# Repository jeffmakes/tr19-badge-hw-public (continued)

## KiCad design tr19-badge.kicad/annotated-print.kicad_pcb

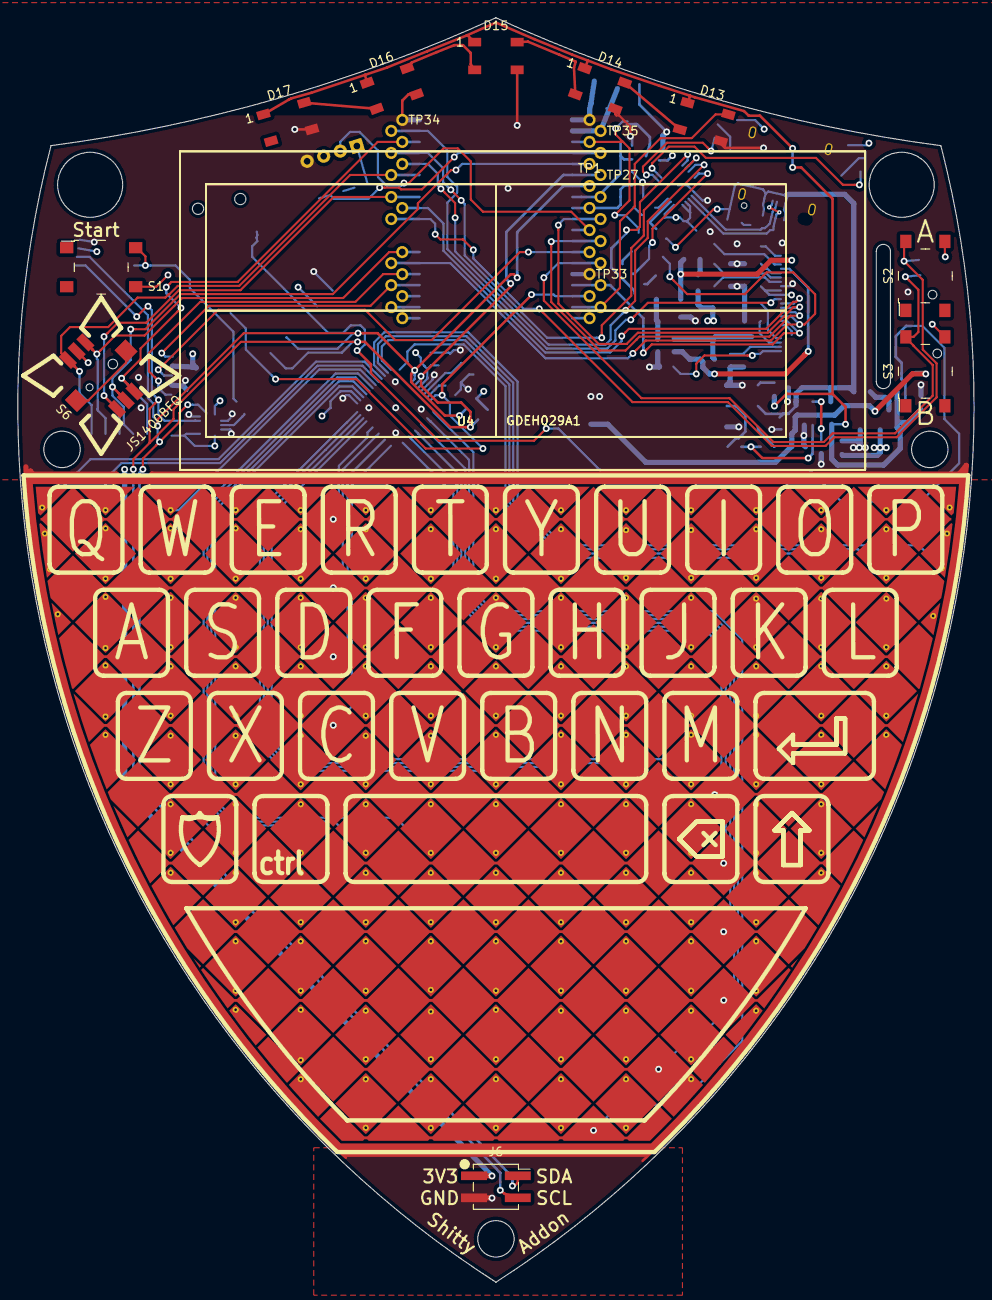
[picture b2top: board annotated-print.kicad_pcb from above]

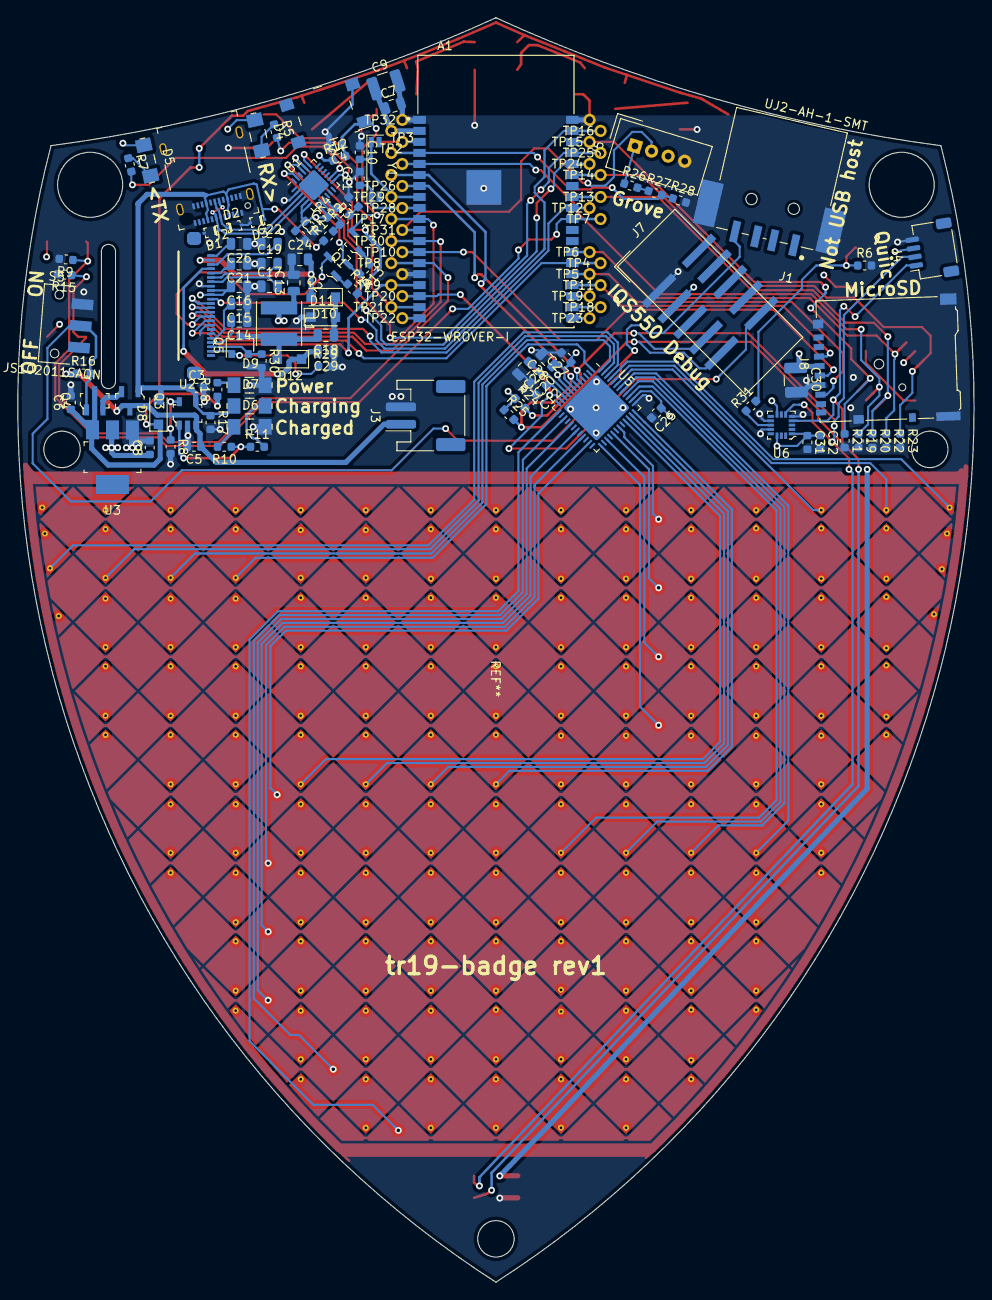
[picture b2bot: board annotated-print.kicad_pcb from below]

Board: 4 copper layers, 110.2 x 145.8 mm, 145 parts (127 on the bottom side), 108 nets.

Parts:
A1: ESP32-WROVER-I; XCVR_ESP32-WROVER-I
A2: tr19_touch_array; electrode-array-2
C1, C3, C5, C6, C8, C31: 4.7uF; C_0603_1608Metric
C2, C4, C12, C25, C32: 100nF; C_0603_1608Metric
C7, C23, C28: 1uF; C_0805_2012Metric
C9, C30: 100uF; C_1210_3225Metric
C10, C11: 10pF; C_0603_1608Metric
C13, C18: 4.7uF 50V; C_0805_2012Metric
C14, C15, C16, C17, C19, C21, C22, C24, C26, C29: 1uF 50V; C_0805_2012Metric
C20, C27: 100pF; C_0603_1608Metric
D1, D2, D3: ESD5Z6.0T5G; SOD-523-numbered-pads
D4, D6: LTST-C150KGKT; 1206
D5, D7: LTST-C150KFKT; 1206
D8, D10, D11, D12: DSS13UTR; D_SOD-123F
D9: LTST-C150KSKT; 1206
D13, D14, D15, D16, D17: WS2812B; LED_WS2812B_PLCC4_5.0x5.0mm_P3.2mm_no-silk
J1: UJ2-AH-1-SMT; CUI_UJ2-AH-1-SMT
J2: 12401610E4_2A; USB_Type_C_Female__12401610E4_2A
J3: S2B-PH-SM4-TB; JST_PH_S2B-PH-SM4-TB_1x02-1MP_P2.00mm_Horizontal
J4: Conn_01x04; JST_SH_SM04B-SRSS-TB_1x04-1MP_P1.00mm_Horizontal
J5: Conn_01x04; NS-Tech_Grove_1x04_P2mm_Vertical
J6: M20-7870246; PinSocket_2x02_P2.54mm_Vertical_SMD
J7: 3020-10-0300-00; IDC-Header_2x05_P2.54mm_Vertical_SMD
J8: Micro_SD_Card_Det_Hirose_DM3AT; microSD_HC_Hirose_DM3AT-SF-PEJM5
L1: 10uH 1A; L_Taiyo-Yuden_MD-5050
Q1, Q2: MMBT3904-TP; SOT-23-3
Q3, Q4: DMG2305UX-13; SOT-23-3
Q5: SSM3K376R; SOT-23
R1, R2, R3, R6, R9, R12, R13, R14, R15, R16, R17, R19, R20, R21, R22, R23, R24, R25, R29: 10k; R_0603_1608Metric
R4, R5, R7, R8, R10, R11, R18, R31: 1k; R_0603_1608Metric
R26, R27, R28: 100k; R_0603_1608Metric
R30: 3R; R_0603_1608Metric
S1, S2, S3, S4: PTS645SM43SMTR92_LFS; Switch_Tactile_SMD_6x6mm_PTS645
S5: JS102011SAQN; SW_JS102011SAQN
S6: JS1400BFQ; SW_JS1400BFQ-arrows
TP1, TP2, TP3, TP4, TP5, TP6, TP7, TP8, TP9, TP10, TP11, TP12, TP13, TP14, TP15, TP16, TP17, TP18, TP19, TP20, TP21, TP22, TP23, TP24, TP25, TP26, TP27, TP28, TP29, TP30, TP31, TP32, TP33, TP34, TP35: test-pad-1.4-TH
U1: CP2102N-A01-GQFN24; QFN-24-1EP_4x4mm_P0.5mm_EP2.6x2.6mm
U2: MCP73831T-2ACI_OT; SOT-753
U3: AP2114H-3_3TRG1; SOT-223
U4, U4#2: GDEH029A1
U5: IQS550; QFN-48-1EP_7x7mm_P0.5mm_EP5.45x5.45mm
U6: LIS3DHTR; VFLGA-16_3x3mm
Y1: 32.768kHz; Crystal_SMD_SeikoEpson_MC146-4Pin_6.7x1.5mm

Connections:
+3V3: A1.2, C1.1, C2.1, C7.1, C8.1, C9.1, C13.1, C16.2, C25.1, C27.1, C28.1, C30.1, C31.1, C32.1, D4.1, D5.1, J4.3, J5.3, J6.2, J7.3, J8.4, L1.1, R4.1, R12.1, R24.1, R25.1, S1.4, S2.4, S3.4, S6.5, TP35.1, U1.5, U1.6, U1.7, U3.2, U4.15, U4.16, U4#2.15, U4#2.16, U5.7, U5.38, U6.1, U6.8, U6.14
+BATT: C5.1, J3.1, Q3.3, R16.1, U2.3
+VSW: C6.1, D8.1, D13.1, D14.1, D15.1, D16.1, D17.1, Q4.3, R18.1, U3.3
/32K_XN: A1.9, C11.1, TP28.1, Y1.2
/32K_XP: A1.8, C10.2, TP29.1, Y1.1
/ACCEL_INT: R31.1, U6.11
/BTN_A: A1.29, R9.1, S2.2, TP7.1
/BTN_B: A1.14, R15.1, S3.2, TP8.1
/BTN_START: R6.1, R31.2, S1.2
/BUSY: A1.16, TP9.1, U4.9, U4#2.9
/DTR: Q2.2, R13.2, U1.23
/EN: A1.3, C4.1, Q1.3, R12.2, S4.1, TP3.1
/GDR: Q5.1, R29.1, U4.2, U4#2.2
/GV_SIG0: J5.1, R26.1
/GV_SIG0_DIV: A1.4, R27.2, R28.1, TP2.1
/GV_SIG1: A1.11, J5.2, TP31.1
/IO0: A1.25, Q2.3, TP4.1, U4.10, U4#2.10
/IQ_RDY: A1.17, J7.10, TP20.1, U5.11
/JOY_A: A1.31, R20.1, S6.1, TP13.1
/JOY_B: A1.33, R23.1, S6.4, TP14.1
/JOY_C: A1.36, R21.1, S6.3, TP15.1
/JOY_D: A1.26, R22.1, S6.6, TP6.1
/JOY_PUSH: A1.5, R19.1, S6.2, TP1.1
/LED_DIN: A1.18, D13.4, TP21.1
/MOSI: A1.37, TP16.1, U4.14, U4#2.14
/PREVGH: C29.2, D12.1, U4.21, U4#2.21
/PREVGL: C24.2, D10.2, U4.23, U4#2.23
/RESE: Q5.2, R30.1, U4.3, U4#2.3
/RTS: Q1.2, R14.2, U1.19
/RXD0: A1.34, TP24.1, U1.21
/RXT: R5.2, U1.13
/Rx0A: A2.RX9, U5.13
/Rx1A: A2.RX8, U5.15
/Rx2A: A2.RX7, U5.17
/Rx3A: A2.RX6, U5.19
/Rx4A: A2.RX5, U5.21
/Rx5A: A2.RX4, U5.23
/Rx6A: A2.RX3, U5.25
/Rx7A: A2.RX2, U5.27
/Rx8A: A2.RX1, U5.29
/Rx9A: A2.RX0, U5.31
/SCK: A1.30, TP12.1, U4.13, U4#2.13
/SCL: A1.6, J4.1, J6.3, J7.9, R25.2, TP27.1, U5.6, U6.4
/SDA: A1.7, J4.2, J6.1, J7.7, R24.2, TP26.1, U5.5, U6.6
/SD_CLK: A1.13, J8.5, TP10.1
/SD_CMD: A1.23, J8.3, TP11.1
/SD_DAT0: A1.24, J8.7, TP5.1
/TXD0: A1.35, TP25.1, U1.20
/TXT: R7.2, U1.14
/Tx0: A2.TX10, U5.33
/Tx1: A2.TX9, U5.34
/Tx2: A2.TX8, U5.35
/Tx3: A2.TX7, U5.36
/Tx4: A2.TX6, U5.39
/Tx5: A2.TX5, U5.40
/Tx6: A2.TX4, U5.41
/Tx7: A2.TX3, U5.42
/Tx8: A2.TX2, U5.43
/Tx9: A2.TX1, U5.44
/Tx10: A2.TX0, U5.45
/Tx11: A2.TX14, U5.46
/Tx12: A2.TX13, U5.47
/Tx13: A2.TX12, U5.48
/Tx14: A2.TX11, U5.1
/USB_DN: D1.1, J2.A7, J2.B7, U1.4
/USB_DP: D2.1, J2.A6, J2.B6, U1.3
/_reserved_gpio6: A1.20, TP23.1
/_reserved_gpio7: A1.21, TP18.1
/_reserved_gpio8: A1.22, TP19.1
/_reserved_gpio11: A1.19, TP22.1
/d_VCOM: C26.2, U4.24, U4#2.24
/d_VDD: C17.2, U4.18, U4#2.18
/d_VGH: C15.2, U4.5, U4#2.5
/d_VGL: C14.2, U4.4, U4#2.4
/d_VPP: C19.2, U4.19, U4#2.19
/d_VSH: C21.2, U4.20, U4#2.20
/d_VSL: C22.2, U4.22, U4#2.22
/~CS~: A1.10, TP17.1, U4.12, U4#2.12
/~DC~: A1.12, TP30.1, U4.11, U4#2.11
/~PWR_EN~: J1.4, Q4.1, R16.2, S5.2
GND: A1.1, A1.15, A1.38, A1.39, A2.GND, C1.2, C2.2, C3.2, C4.2, C5.2, C6.2, C7.2, C8.2, C9.2, C10.1, C11.2, C12.2, C13.2, C14.1, C15.1, C16.1, C17.1, C19.1, C20.2, C21.1, C22.1, C23.2, C24.1, C25.2, C26.1, C27.2, C28.2, C29.1, C30.2, C31.2, C32.2, D1.2, D2.2, D3.2, D6.2, D9.2, D11.1, D13.3, D14.3, D15.3, D16.3, D17.3, J1.S1, J1.S2, J2.A1, J2.A12, J2.B1, J2.B12, J2.SH, J3.2, J4.4, J5.4, J6.4, J7.1, J8.6, J8.11, R3.2, R6.2, R8.2, R9.2, R15.2, R17.2, R19.2, R20.2, R21.2, R22.2, R23.2, R28.2, R29.2, R30.2, S4.3, S5.1, TP32.1, TP33.1, TP34.1, U1.2, U1.25, U2.2, U3.1, U4.8, U4.17, U4#2.8, U4#2.17, U5.8, U5.37, U5.49, U6.5, U6.10, U6.12
unnamed: C12.1, U5.10
unnamed: C18.1, D10.1, D11.2
unnamed: C18.2, D12.2, L1.2, Q5.3
unnamed: C20.1, C23.1, U5.9
unnamed: D4.2, R5.1
unnamed: D5.2, R7.1
unnamed: D6.1, R10.2
unnamed: D7.2, R11.2
unnamed: D9.1, R18.2
unnamed: D13.2, D14.4
unnamed: D14.2, D15.4
unnamed: D15.2, D16.4
unnamed: D16.2, D17.4
unnamed: Q1.1, R13.1
unnamed: Q2.1, R14.1
unnamed: Q3.2, Q4.2
unnamed: R1.2, R2.1, U1.8
unnamed: R2.2, R3.1
unnamed: R4.2, U1.9
unnamed: R8.1, U2.5
unnamed: R10.1, R11.1, U2.1
unnamed: R26.2, R27.1
unnamed: S6.SH1, S6.SH2
unnamed: U4.1, U4#2.1
unnamed: U4.6, U4#2.6
unnamed: U4.7, U4#2.7
VBUS: C3.1, D3.1, D7.1, D8.2, J2.A4, J2.A9, J2.B4, J2.B9, Q3.1, R1.1, R17.1, U2.4

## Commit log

2019-07-17 Troopers19 hardware deisgn for public release
